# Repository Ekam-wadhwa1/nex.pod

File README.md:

# nex.pod
nexpod is a compact device that can be added in any case or retrofitted in old cases  of devices like charger cases old plastic boxes or even make a pcb, and more to have a companion and be coded to display whatever you want and be used in any way possible,it all depends on your creativity.

## note
the code given is just a demo what you can do and how you can use it
you can write your own code and make it do whatever you want

## demo
https://wokwi.com/projects/462925725106226177

### tags

# author
made by ekam wadhwa
founder, 
nexus 

### star the project if you wanna support me

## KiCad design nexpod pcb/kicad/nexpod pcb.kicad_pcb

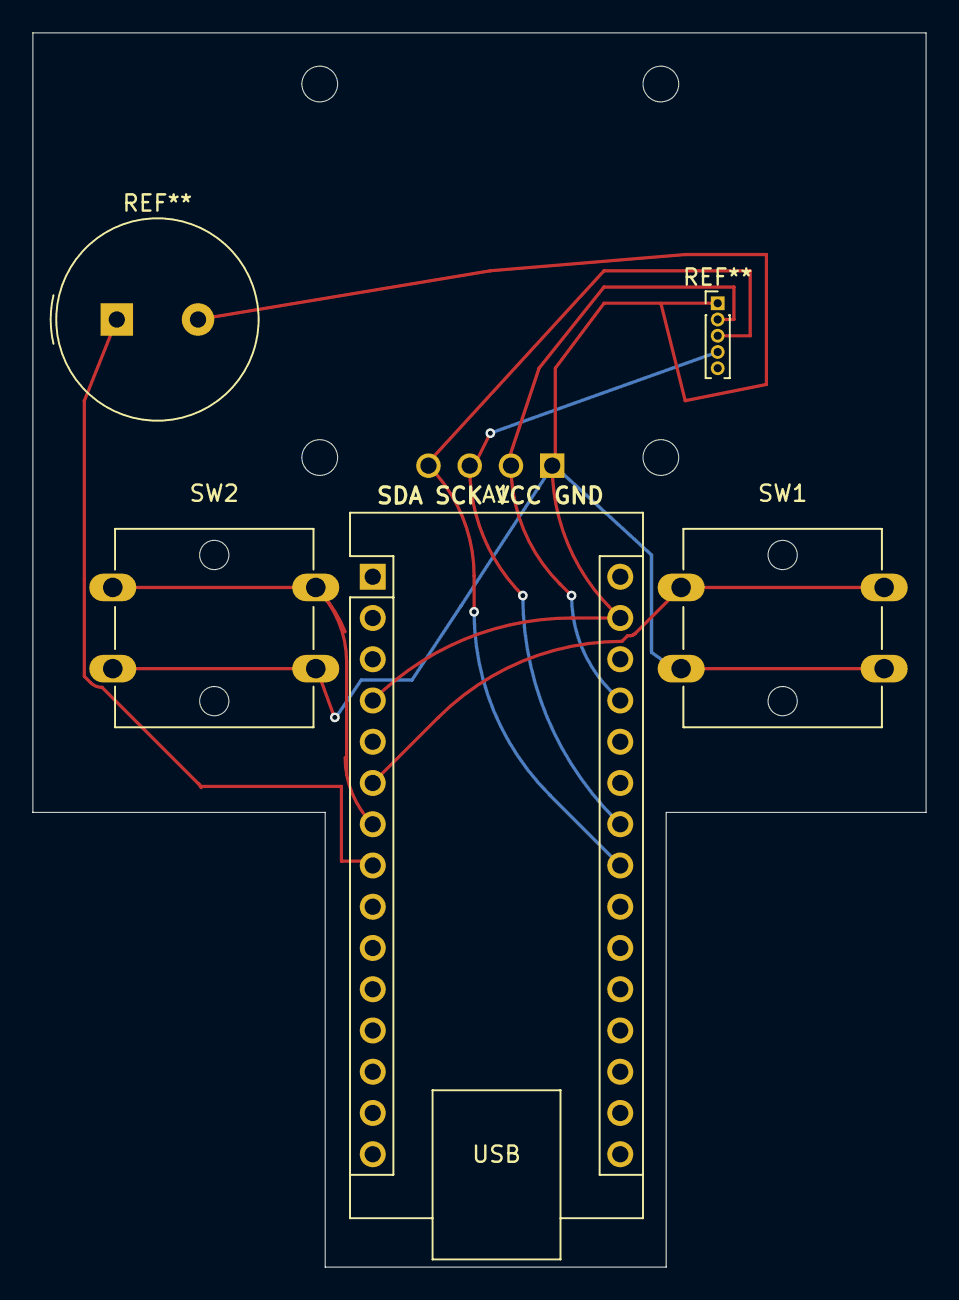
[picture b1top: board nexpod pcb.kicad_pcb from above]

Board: 2 copper layers, 55.0 x 76.0 mm, 4 parts (0 on the bottom side), 6 nets.

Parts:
A1: Arduino_Nano_v3.x; Arduino_Nano
J1: OLED_128x64
SW1, SW2: SW_Push_Dual; SW_SPST_Omron_B3F-40xx

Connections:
unnamed: A1.27 (+5V), J1.2 (VCC)
unnamed: A1.23 (A4), J1.4 (SDA)
unnamed: A1.24 (A5), J1.3 (SCL)
unnamed: A1.6 (D3), SW1.1
unnamed: A1.7 (D4), SW2.1
unnamed: A1.4 (GND), A1.29 (GND), J1.1 (GND)

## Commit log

2026-05-01 Enhance README with project details and features
    Expanded README with detailed features, controls, hardware used, and future improvements.
2026-05-16 Remove KICAD badge from README
    Removed KICAD badge from the README.
2026-05-28 Add demo section with project link
    Added demo link to README
2026-06-05 Refactor display handling and button logic
2026-06-05 Add u8g2lib to libraries list
